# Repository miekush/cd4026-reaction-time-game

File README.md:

# CD4026_Reaction_Time_Game
A CD4026 / NE555 based Reaction Time Game with Latching Input Switches

Designed by Mike Kushnerik (MKE) in KiCad V5

# Enclosure

To make things look nicer, I designed a simple 3D printable enclosure to mount the PCB and a 9V battery. 

See the Enclosure folder for design files and STL!

# License

MKE supports the open source hardware community by sharing hardware design files freely on GitHub!

Please support MKE by purchasing products on [Tindie](https://www.tindie.com/stores/mkengineering/)!

Designed by Mike Kushnerik for MKEngineering

Licensed under [Creative Commons Attribution-ShareAlike CC BY-SA 3.0](http://creativecommons.org/licenses/by-sa/3.0/)

All text above must be included in any redistribution!

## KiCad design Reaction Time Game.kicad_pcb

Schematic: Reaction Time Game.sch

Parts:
C1, C2, C3, C4, C5, C6: 0.1uF; C_Disc_D4.3mm_W1.9mm_P5.00mm
D1: 5819; D_DO-41_SOD81_P7.62mm_Horizontal
D2: START; LED_D5.0mm
D3: STOP; LED_D5.0mm
DS1: SC56-11SRWA
H1, H2, H3, H4: MT; MountingHole_3.2mm_M3
Q1: 2N3906; TO-92_Inline_Wide
Q2: 2N3904; TO-92_Inline_Wide
R2, R3, R4, R5: 1K; R_Axial_DIN0204_L3.6mm_D1.6mm_P5.08mm_Horizontal
RV1: 1M; Potentiometer_Runtron_RM-065_Vertical
SW1: POWER; OS102011MA1QN1_RA
SW2: STOP; SW_PUSH_6mm
SW3: START; SW_PUSH_6mm
TP1: BAT+; WIRE_SR_C
TP2: BAT-; WIRE_SR_R
U1: NE555P; DIP-8_W7.62mm
U2: CD4026; DIP-16_W7.62mm

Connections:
+9V: C5.2, C6.2, Q1.1 (E), R2.1, SW1.2 (B), U1.8, U2.3, U2.16
GND: C1.1, C2.1, C3.1, C4.1, C5.1, C6.1, D2.1 (K), DS1.3, DS1.8, Q2.1 (E), R5.2, SW2.2, SW3.2, TP2.1, U1.1, U1.4, U2.8, U2.15
unnamed: C1.2, Q1.3 (C), R4.1, U2.2
unnamed: C2.2, RV1.1, U1.2, U1.6
unnamed: C3.2, D3.1 (K), Q2.3 (C), R3.2, SW2.1
unnamed: C4.2, Q2.2 (B), R4.2, R5.1, SW3.1
unnamed: D1.1 (K), SW1.1 (A)
unnamed: D1.2 (A), TP1.1
unnamed: D2.2 (A), D3.2 (A), R2.2
unnamed: DS1.1, U2.11
unnamed: DS1.2, U2.9
unnamed: DS1.4, U2.13
unnamed: DS1.6, U2.12
unnamed: DS1.7, U2.10
unnamed: DS1.9, U2.6
unnamed: DS1.10, U2.7
unnamed: Q1.2 (B), R3.1
unnamed: RV1.2, U1.3, U2.1

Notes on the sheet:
Counter and Display Circuit
Input Supply
Mounting Holes

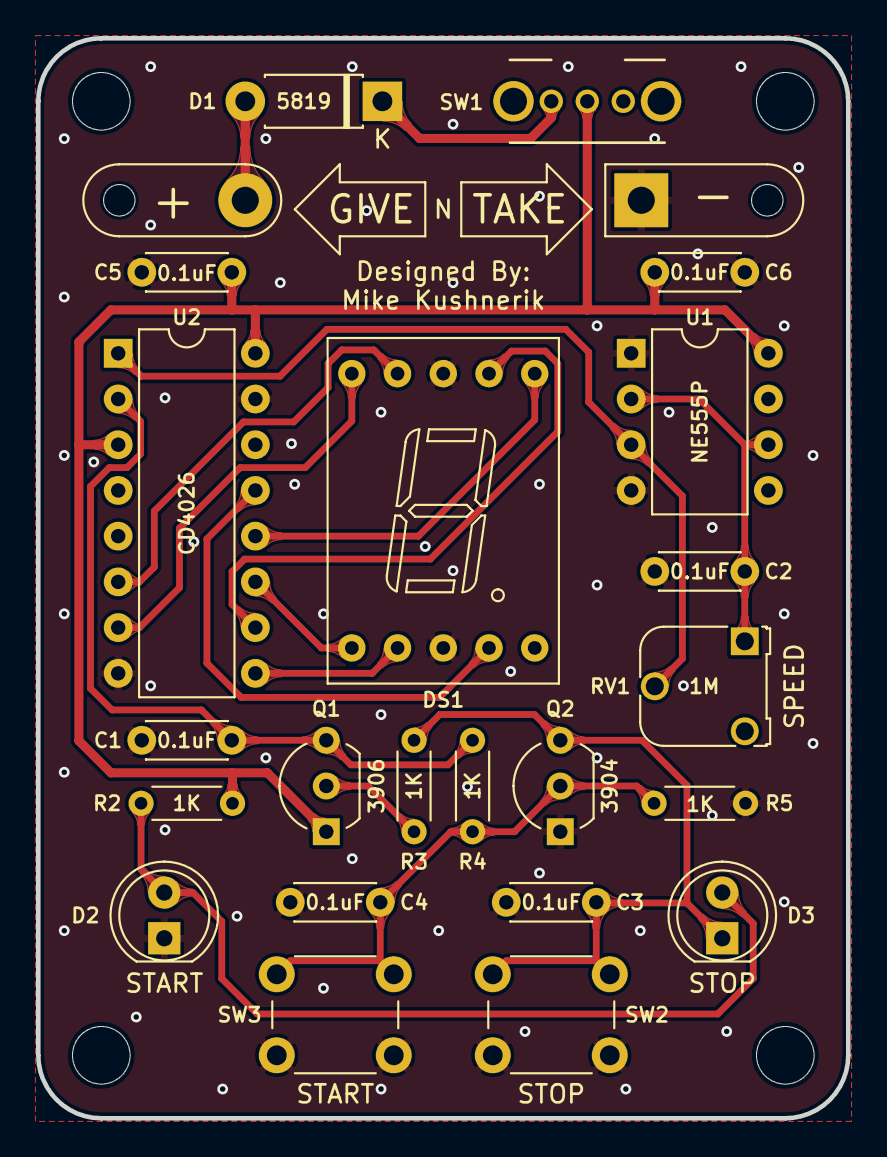
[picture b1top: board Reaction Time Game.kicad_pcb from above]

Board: 2 copper layers, 45.0 x 60.0 mm, 28 parts (0 on the bottom side), 18 nets.

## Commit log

2020-12-27 Add KiCad Files
2020-12-27 Add Revision 1A Schematic
2020-12-27 Add Images to README
2020-12-29 Added POR Circuit for CD4026
2020-12-29 Add 1B Images
2021-01-08 Update License
2021-01-08 Add Enclosure Image
2021-01-08 Add Enclosure Images
2021-01-08 Update 1B Images

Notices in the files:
Reaction Time Game.sch:
http://creativecommons.org/licenses/by-sa/4.0
Licensed under Creative Commons Attribution-ShareAlike CC BY-SA 4.0
